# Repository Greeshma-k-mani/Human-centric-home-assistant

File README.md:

# EVA — Human Centered Embodied Home Assistant 🤖

> Voice-activated home assistant robot with face recognition, radar presence detection,
> expressive head movement, and smart home automation.
> 
> 🥇 **First Place — INNOVIX, RISE 2026 | FISAT ECE Department**

---

## 🧠 What is EVA?

EVA is a fully functional human-centric home assistant robot built on **Raspberry Pi 2 + ESP32**,
designed to recognize users, navigate to them, and assist through natural voice interaction.

Unlike conventional voice assistants, EVA physically moves to the user, verifies identity
through face recognition, and responds with expressive animations — making interaction
more natural and personal.

---

## ⚙️ System Architecture

```
┌─────────────────────────────────────────┐
│         RASPBERRY PI 2 MODEL B          │
│  Face Recognition · Voice · Navigation  │
│  Intent Engine · Flask Web UI · Groq AI │
└──────────────┬──────────────────────────┘
               │ HTTP (WiFi)
┌──────────────▼──────────────────────────┐
│              ESP32 WROOM-32             │
│  Motors · Servos · TFT · Radar · Face  │
└──────────────────────────────────────────┘
               │ HTTP (WiFi)
┌──────────────▼──────────────────────────┐
│            ESP8266 NodeMCU              │
│     Garden Relay · Light Control        │
└──────────────────────────────────────────┘
```

---

## 🔧 Features

| Feature | Details |
|---------|---------|
| 🎙️ Wake Word | Porcupine — "Hey Eva" |
| 👁️ Face Recognition | OpenCV — Haar + LBPH |
| 📡 Presence Detection | LD2410 mmWave Radar |
| 😊 Face Display | ST7735R TFT — 6 bitmap expressions |
| 🤖 3-DoF Head | MG90S servos — Yaw · Pitch · Roll |
| 🚗 Navigation | TB6612FNG + N25 gear motors |
| 🏠 Home Automation | ESP8266 relay — pump + lights |
| 🧠 AI Conversation | Groq LLM (Llama 3) |
| 🌐 Web UI | Flask dashboard — auth + controls |
| 🔌 Custom PCB | KiCad 9.0.5 — full system integration |
| 🖨️ Body | 3D printed enclosure (PLA) |

---

## 🛠️ Hardware

- Raspberry Pi 2 Model B
- ESP32 WROOM-32 DevKit
- ESP8266 NodeMCU
- Pi Camera Module V2 (NoIR)
- ST7735R TFT Display
- HLK-LD24 mmWave Radar
- TB6612FNG Motor Driver
- N25 Metal Gear Motors × 2
- MG90S Servo Motors × 3
- PAM8403 Audio Amplifier
- Custom PCB (KiCad 9.0.5)
- 2S Li-ion Battery (7.4V)

---

## 💻 Software Stack

```python
stack = {
    "Pi"      : ["Python 3", "OpenCV", "Porcupine", "Flask",
                 "edge-TTS", "Google STT", "Groq LLM"],
    "ESP32"   : ["Arduino C++", "WebServer", "SPI", "LEDC PWM"],
    "ESP8266" : ["Arduino C++", "ESP8266WebServer"],
    "PCB"     : ["KiCad 9.0.5"],
    "Body"    : ["Fusion 360", "3D Printing (PLA)"],
}
```

---

## 📬 Contact

---

GitHub: https://github.com/Greeshma-k-mani

LinkedIn: https://www.linkedin.com/in/greeshma-k-mani

<p align="center"><i>Built with curiosity. Powered by embedded silicon. Driven by the need to build things that actually work.</i></p>

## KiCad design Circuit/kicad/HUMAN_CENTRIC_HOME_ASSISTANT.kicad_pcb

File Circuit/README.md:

# PCB Design — EVA Human Centered Embodied Home Assistant

Circuit schematic and PCB layout for the EVA project, designed using **KiCad 9.0.5**.

---

## 📋 System Overview

| Controller | Role |
|------------|------|
| **Raspberry Pi 2 Model B** | Face recognition, voice interaction, navigation logic, Flask web UI |
| **ESP32 WROOM-32** | Motors, servos, TFT display, radar, HTTP server |
| **ESP8266 NodeMCU** | Garden relay control, WiFi automation |

---

## 🔌 Peripherals

| Component | Interface |
|-----------|-----------|
| ST7735R TFT Display | SPI |
| MG90S Servo × 3 (Yaw, Pitch, Roll) | PWM |
| TB6612FNG Motor Driver | PWM + GPIO |
| N25 Gear Motors × 2 | TB6612FNG |
| HLK-LD24 mmWave Radar | UART2 |
| 2-Channel Relay Module | GPIO (ESP8266) |
| PAM8403 Audio Amplifier | GPIO |

---

## ⚡ Power Architecture

- **Source:** 2S Li-ion Battery (7.4V)
- **MINI560:** 5V regulated — Raspberry Pi
- **Mini360:** 3.3V regulated — ESP32, ESP8266, logic
- **LM2590:** 6V regulated — Motors and servos
- **Protection:** 10A fuse + power switch
- **Decoupling:** Bulk and bypass capacitors on all power rails

---

## 📐 PCB Design Status

| Item | Status |
|------|--------|
| Schematic | ✅ Completed |
| PCB Layout | ✅ Completed |
| 3D Render | ✅ Completed |
| Fabrication | ✅ Fabricated |
| Testing | ✅ Tested |
| Design Tool | KiCad 9.0.5 |

---

---

## 📝 Design Notes

- Common ground reference across all modules
- Decoupling capacitors placed close to all ICs
- High-current motor and servo rails isolated from logic rails
- Designed for low-voltage, non-safety-critical academic use

---

> This PCB is part of an academic embedded systems project and is not intended for commercial or safety-critical applications.

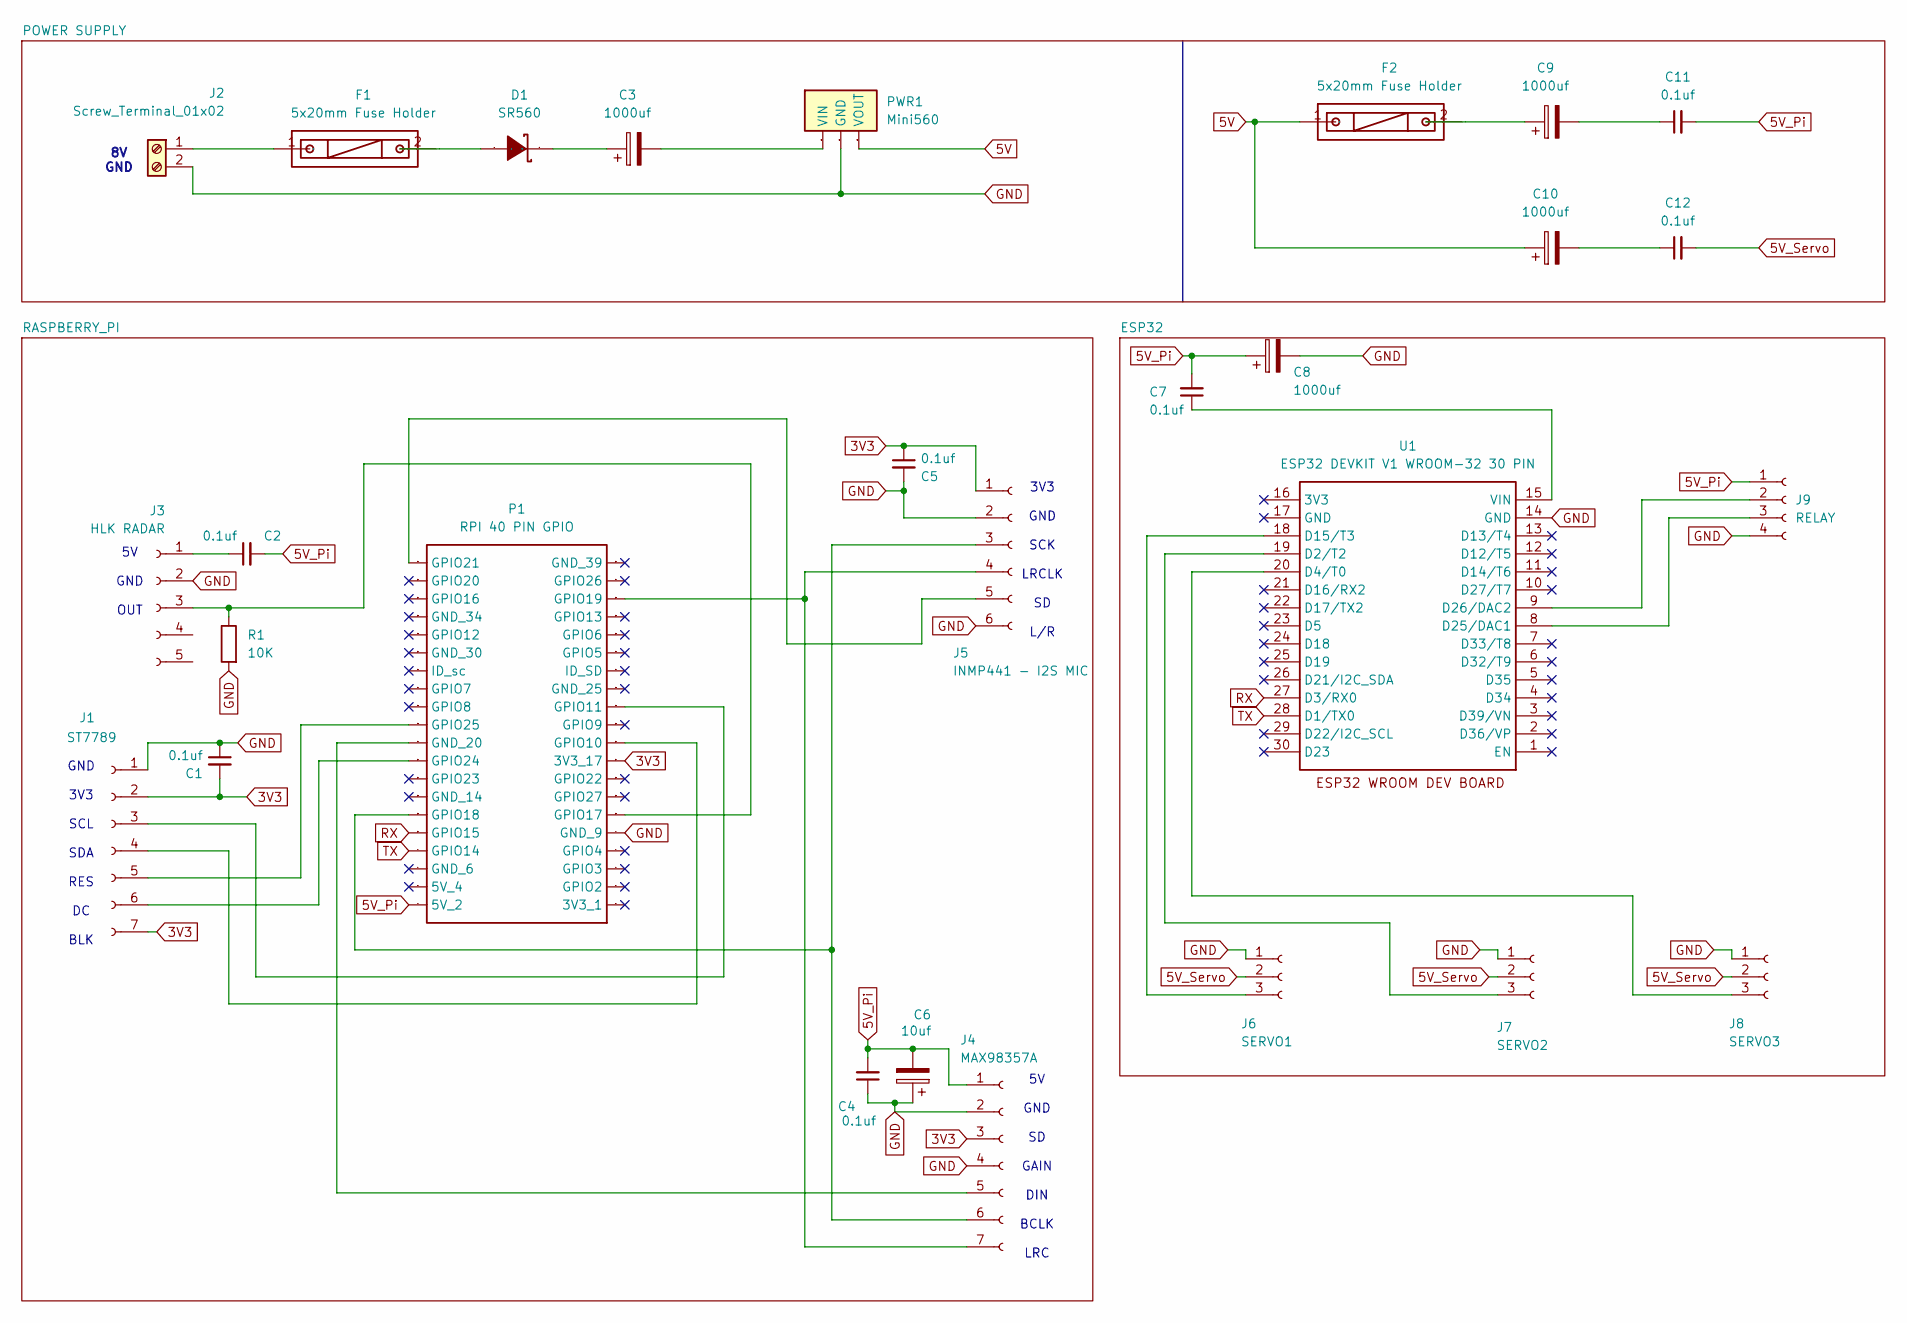
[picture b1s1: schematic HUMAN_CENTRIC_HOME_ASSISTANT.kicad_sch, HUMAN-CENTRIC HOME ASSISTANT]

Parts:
C1, C2, C4, C5, C7, C11, C12: 0.1uf; C_Disc_D5.0mm_W2.5mm_P5.00mm
C3, C8, C9, C10: 1000uf; CP_Radial_D10.0mm_P5.00mm
C6: 10uf; CP_Radial_D6.3mm_P2.50mm
D1: SR560; SR560 Schottky Barrier Rectifier Diode 5A; Manufacturer Part SR560
F1, F2: 5x20mm Fuse Holder; 5X20-FUSE
J1: ST7789; PINHEADER_1X07_P2.54MM_VERTICAL
J2: Screw_Terminal_01x02; SCREWTERMINAL-5MM-2-DW
J3: HLK RADAR; PINHEADER_1X05_P2.54MM_VERTICAL
J4: MAX98357A; PINHEADER_1X07_P2.54MM_VERTICAL
J5: INMP441 - I2S MIC; CONNECTOR_PINHEADER_2.54MMPINHEADER_1X06_P2.54MM_VERTICAL
J6: SERVO1; CONN-HEADER-STRAIGHT-P2.54MM-1X03
J7: SERVO2; CONN-HEADER-STRAIGHT-P2.54MM-1X03
J8: SERVO3; CONN-HEADER-STRAIGHT-P2.54MM-1X03
J9: RELAY; PINSOCKET_1X04_P2.54MM_VERTICAL
P1: RPI 40 PIN GPIO; 2X20-PIN-HEADER
PWR1: Mini560; MINI560; Manufacturer Part mini560
R1: 10K; R_Axial_DIN0207_L6.3mm_D2.5mm_P7.62mm_Horizontal
U1: ESP32 DEVKIT V1 WROOM-32 30 PIN; ESP32 DEVKIT V1 30 PIN

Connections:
3V3: C1.2, C5.1, J1.2, J1.7, J4.3, J5.1, P1.17 (3V3_17)
5V: C10.1, F2.1, PWR1.VOUT
5V_Pi: C2.2, C4.2, C6.2, C7.2, C8.1, C11.2, J4.1, J9.1, P1.2 (5V_2)
5V_Servo: C12.2, J6.2, J7.2, J8.2
GND: C1.1, C4.1, C5.2, C6.1, C8.2, J1.1, J2.2, J3.2, J4.2, J4.4, J5.2, J5.6, J6.1, J7.1, J8.1, J9.4, P1.9 (GND_9), PWR1.GND, R1.1, U1.14 (GND)
unnamed: C3.2, PWR1.VIN
unnamed: C9.1, F2.2
unnamed: C10.2, C12.1
unnamed: C9.2, C11.1
unnamed: D1.1 (A), F1.2
unnamed: C3.1, D1.2 (K)
unnamed: J1.3, P1.23 (GPIO11)
unnamed: J1.4, P1.19 (GPIO10)
unnamed: J1.5, P1.22 (GPIO25)
unnamed: J1.6, P1.18 (GPIO24)
unnamed: F1.1, J2.1
unnamed: C2.1, J3.1
unnamed: J3.3, P1.11 (GPIO17), R1.2
unnamed: J4.5, P1.20 (GND_20)
unnamed: J4.6, J5.3, P1.12 (GPIO18)
unnamed: J4.7, J5.4, P1.35 (GPIO19)
unnamed: J5.5, P1.40 (GPIO21)
unnamed: J6.3, U1.18 (D15/T3)
unnamed: J7.3, U1.19 (D2/T2)
unnamed: J8.3, U1.20 (D4/T0)
unnamed: J9.2, U1.9 (D26/DAC2)
unnamed: J9.3, U1.8 (D25/DAC1)
unnamed: C7.1, U1.15 (VIN)
RX: P1.10 (GPIO15), U1.27 (D3/RX0)
TX: P1.8 (GPIO14), U1.28 (D1/TX0)

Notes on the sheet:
8V GND
3V3 GND SCK LRCLK SD L/R
GND 3V3 SCL SDA RES DC BLK
5V GND SD GAIN DIN BCLK LRC
5V GND OUT

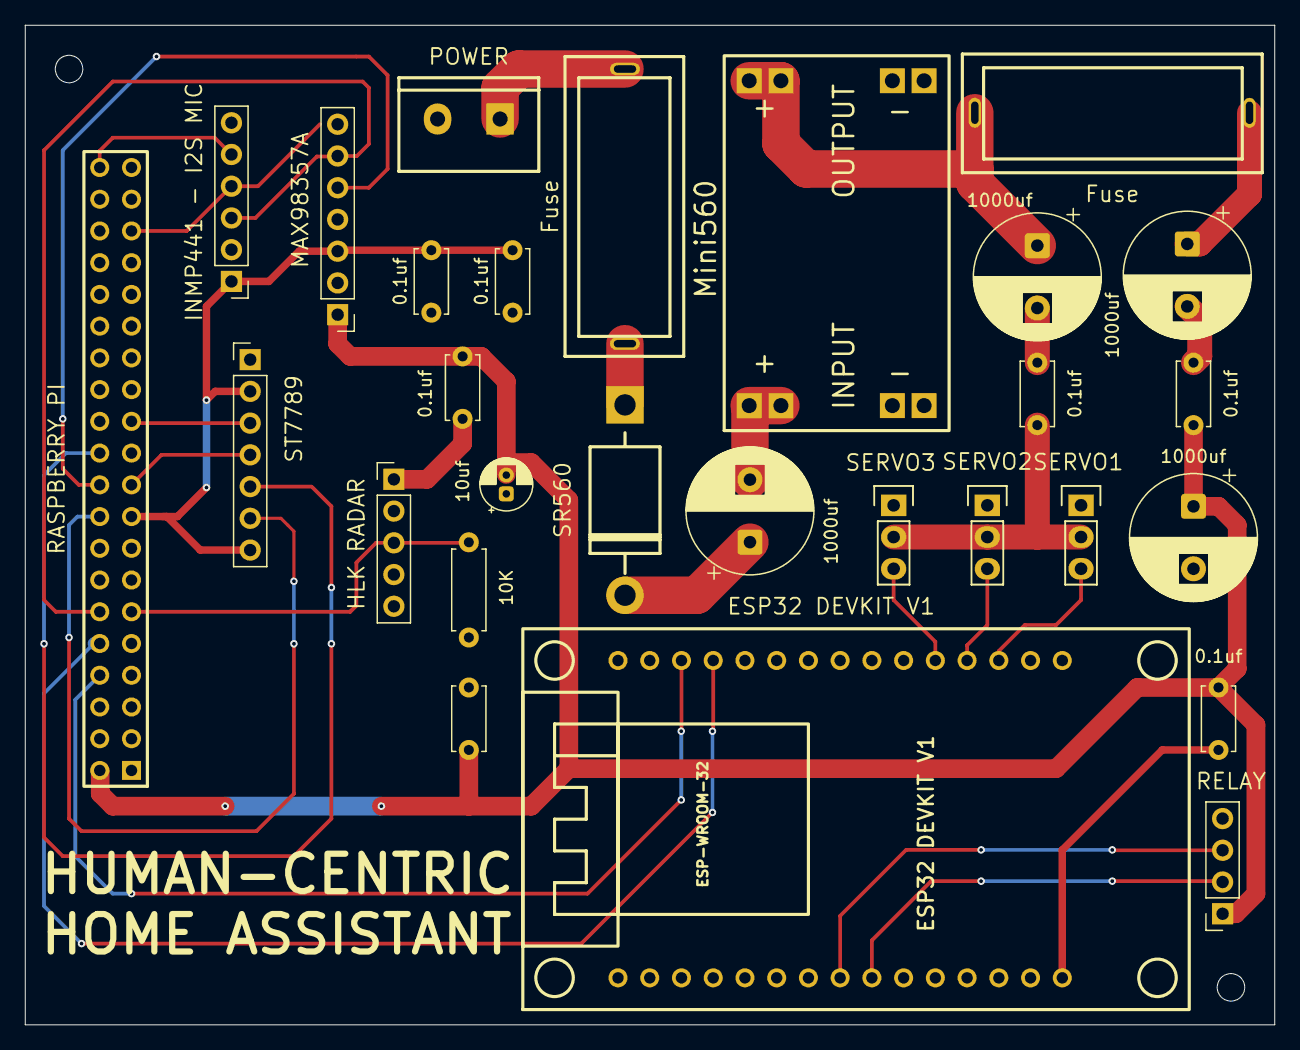
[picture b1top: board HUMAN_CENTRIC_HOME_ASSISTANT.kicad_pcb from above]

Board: 2 copper layers, 100.0 x 80.0 mm, 28 parts (0 on the bottom side), 30 nets.

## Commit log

2025-12-25 Revise README with project details and objectives
    Updated project title and added detailed project overview, objectives, system architecture, current status, and tools used.
2025-12-25 Add README for 3 DOF Servo-Based Head Mechanism
    Added detailed documentation for the mechanical design and implementation of a 3-DOF servo-based head mechanism, including design overview, fabrication methods, and current status.
2025-12-25 Create gitkeep
2026-06-28 Revise README for EVA home assistant project
    Updated project title and overview, added sections on system architecture and features, and improved formatting.
2026-06-28 Create docs
2026-06-28 Revise README for 3DOF head mechanical design
    Updated the README to reflect the 3DOF head design and removed outdated sections.
2026-06-29 Update PCB files
